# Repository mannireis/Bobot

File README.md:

# Bobot

Ever wondered how a 555 timer IC worked? Here you have it! A 555 IC, made entirely with THT transistors.

## Schematic
 
## PCB

## Features
- Low power design! 3V operating voltage
- Awesome Robot cat design!
- Keychain!

## How to build
Just order the PCB & components, open up the KiCAD file and build it accordingly.

## BOM
- 1 	Battery holder
- 2 	220 ohm resistors
- 1 	Push Button

Made by `@manni` on slack :3

Not copying `@cyao`'s readme trust!

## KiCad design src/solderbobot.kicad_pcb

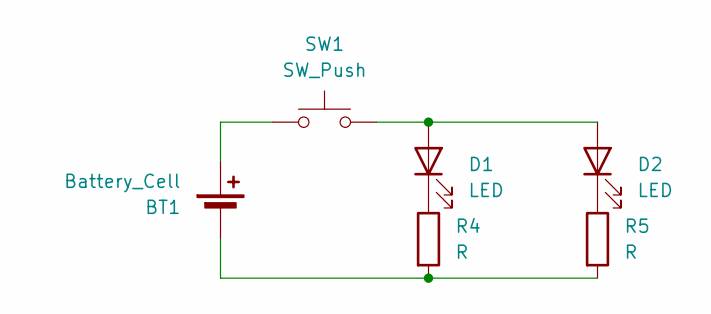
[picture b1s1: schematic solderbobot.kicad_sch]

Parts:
BT1: Battery_Cell; BatteryHolder_Keystone_3034_1x20mm
D1, D2: LED; LED_D5.0mm
R4, R5: R; R_Axial_DIN0207_L6.3mm_D2.5mm_P7.62mm_Horizontal
SW1: SW_Push; SW_PUSH_6mm

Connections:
unnamed: BT1.1 (+), SW1.1
unnamed: BT1.2 (-), R4.2, R5.2
unnamed: D1.2 (A), D2.2 (A), SW1.2
unnamed: D1.1 (K), R4.1
unnamed: D2.1 (K), R5.1

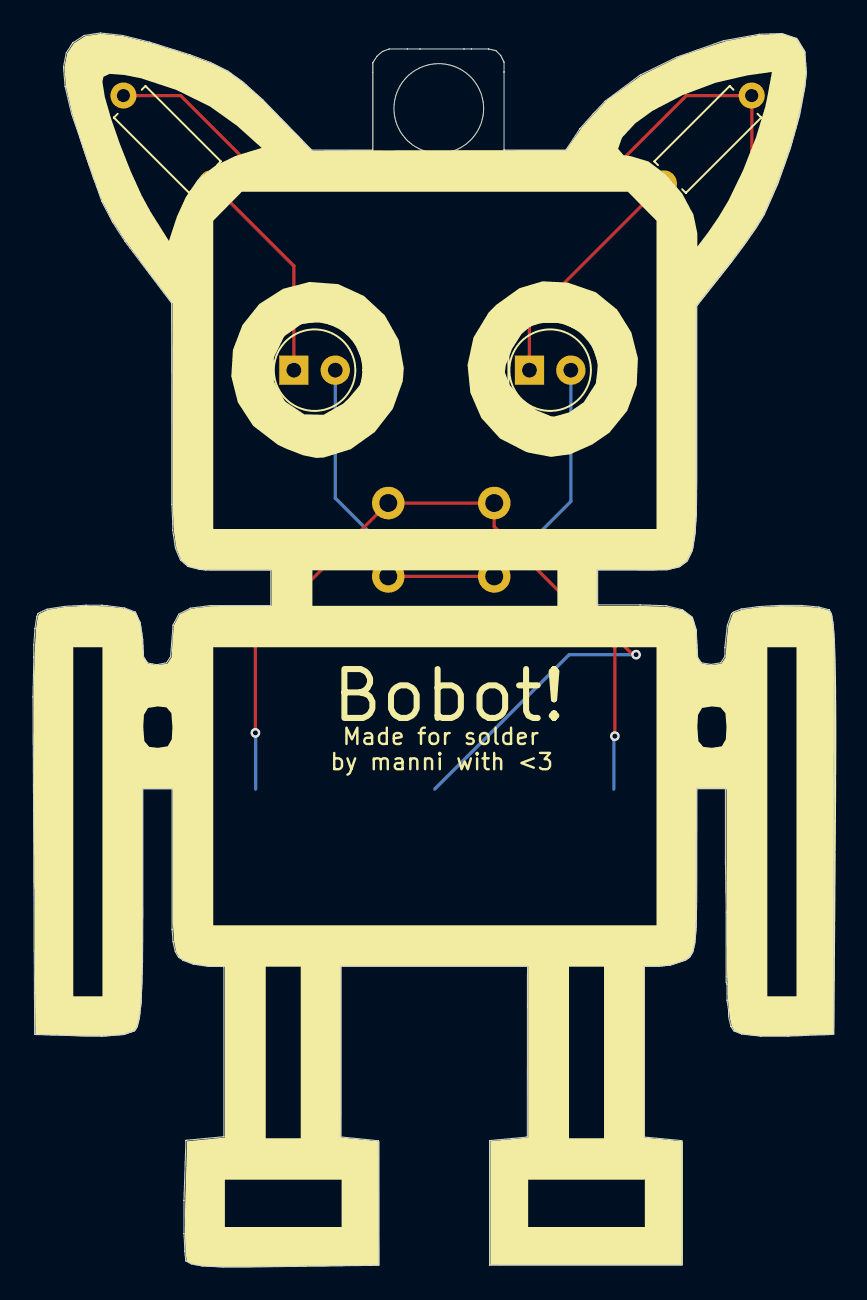
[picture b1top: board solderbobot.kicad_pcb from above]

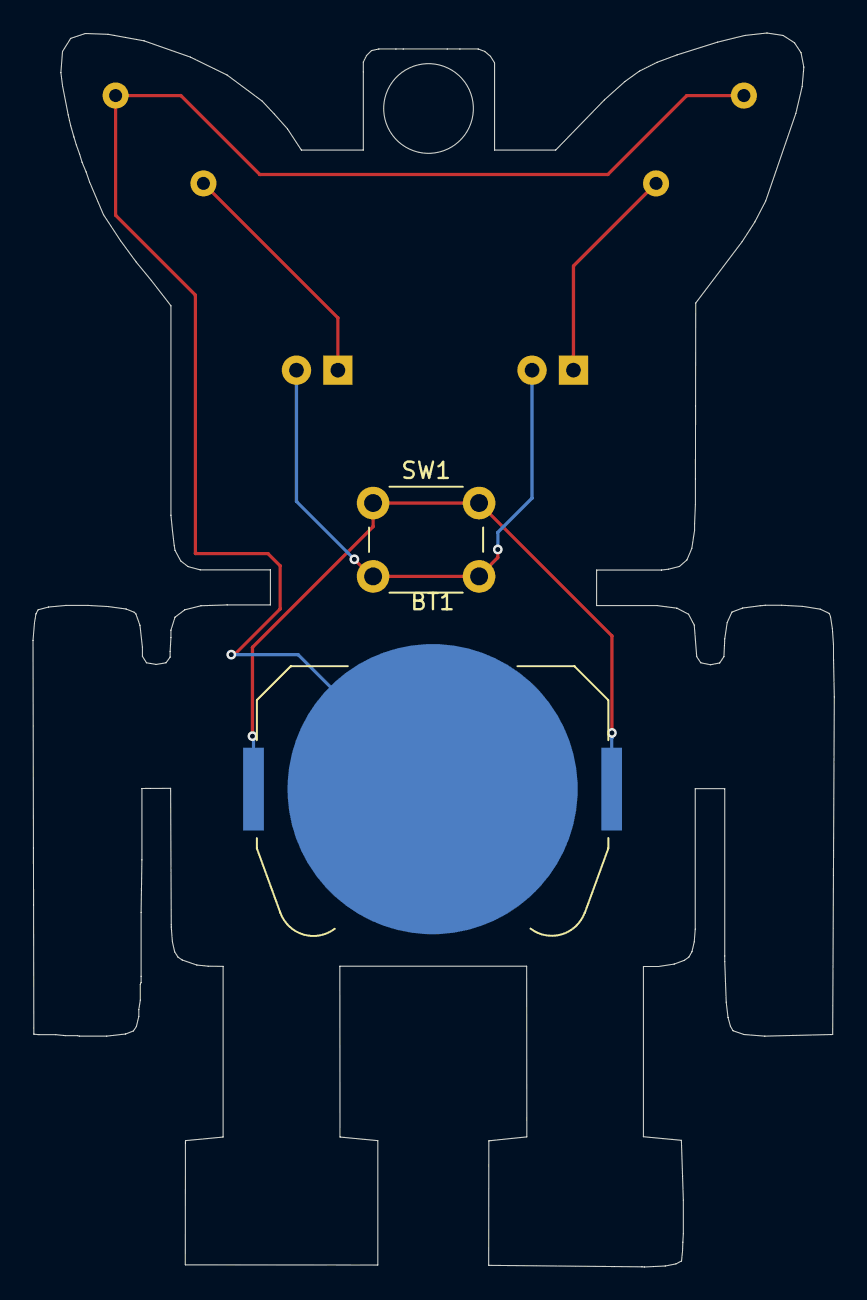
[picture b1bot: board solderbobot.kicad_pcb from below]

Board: 2 copper layers, 49.2 x 75.7 mm, 6 parts (2 on the bottom side), 5 nets.

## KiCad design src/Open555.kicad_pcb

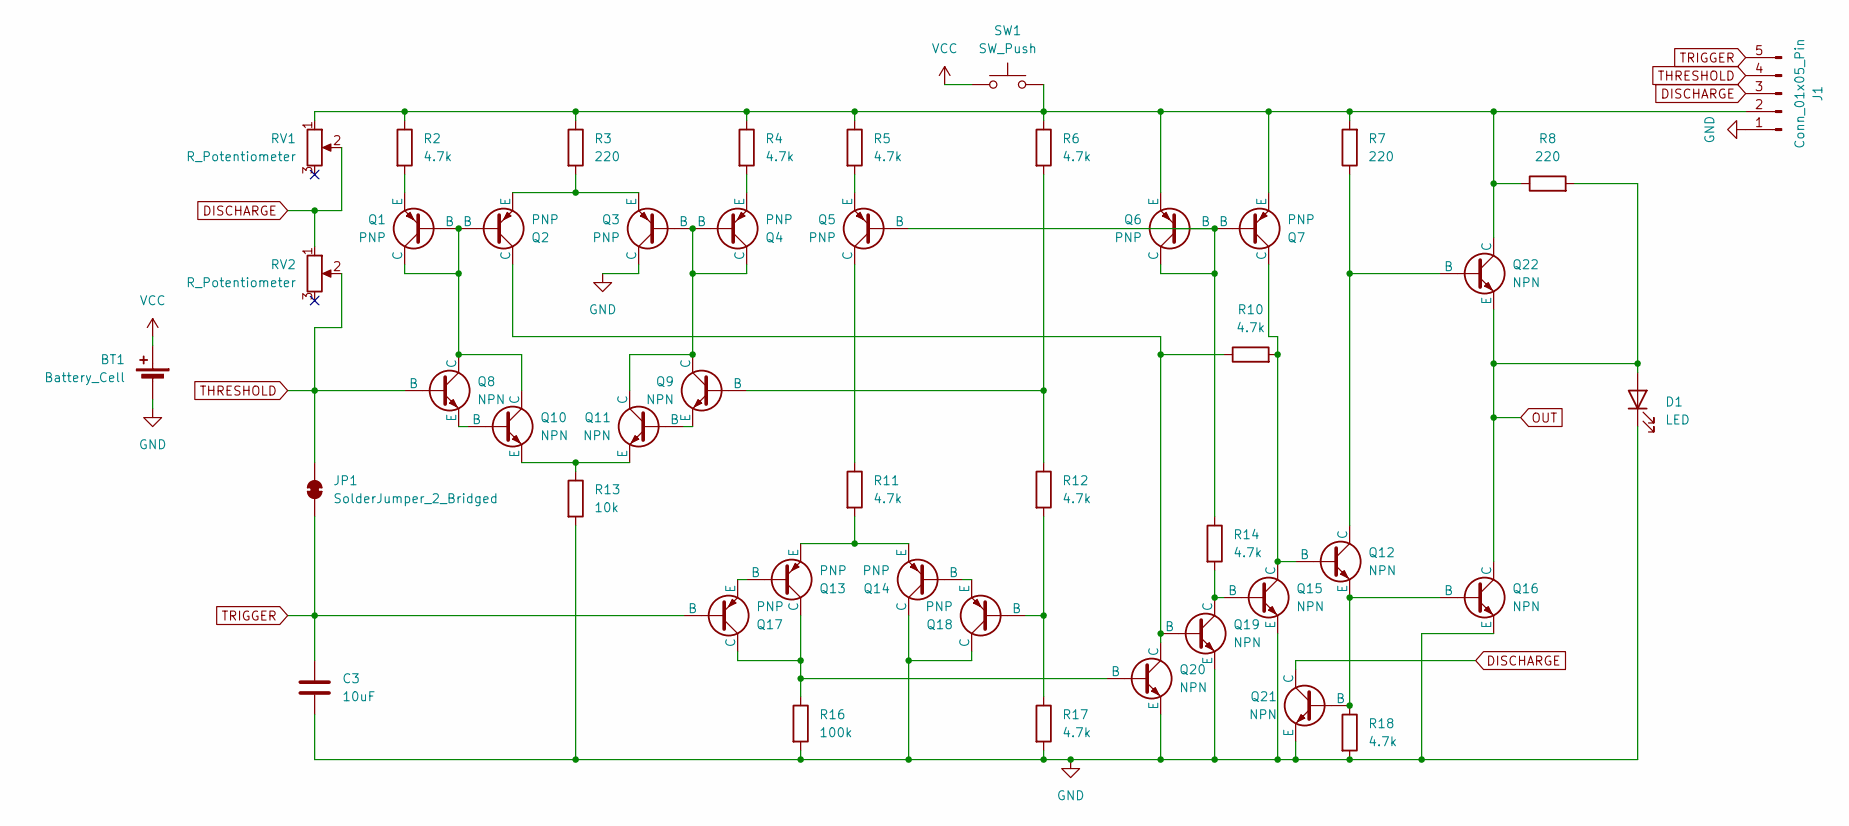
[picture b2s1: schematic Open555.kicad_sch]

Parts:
BT1: Battery_Cell; BatteryHolder_Multicomp_BC-2001_1x2032
C3: 10uF; CP_Radial_D8.0mm_P5.00mm
D1: LED; LED_D5.0mm
J1: Conn_01x05_Pin; PinHeader_1x05_P2.54mm_Vertical
JP1: SolderJumper_2_Bridged; SolderJumper-2_P1.3mm_Bridged2Bar_RoundedPad1.0x1.5mm
Q1, Q2, Q3, Q4, Q5, Q6, Q7, Q13, Q14, Q17, Q18: PNP; TO-92L_HandSolder
Q8, Q9, Q10, Q11, Q12, Q15, Q16, Q19, Q20, Q21, Q22: NPN; TO-92L_HandSolder
R2, R4, R5, R6, R10, R11, R12, R14, R17, R18: 4.7k; R_Axial_DIN0207_L6.3mm_D2.5mm_P7.62mm_Horizontal
R3, R7, R8: 220; R_Axial_DIN0207_L6.3mm_D2.5mm_P7.62mm_Horizontal
R13: 10k; R_Axial_DIN0207_L6.3mm_D2.5mm_P7.62mm_Horizontal
R16: 100k; R_Axial_DIN0207_L6.3mm_D2.5mm_P7.62mm_Horizontal
RV1, RV2: R_Potentiometer; Potentiometer_Runtron_RM-065_Vertical
SW1: SW_Push; SW_PUSH_6mm

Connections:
DISCHARGE: J1.3, Q21.1 (C), RV1.2, RV2.1
GND: BT1.2 (-), C3.2, D1.1 (K), J1.1, Q3.1 (C), Q14.1 (C), Q15.3 (E), Q16.3 (E), Q18.1 (C), Q19.3 (E), Q20.3 (E), Q21.3 (E), R13.2, R16.2, R17.2, R18.2
unnamed: J1.2, Q6.3 (E), Q7.3 (E), Q22.1 (C), R2.1, R3.1, R4.1, R5.1, R6.1, R7.2, R8.1, RV1.1, SW1.2
unnamed: Q1.1 (C), Q1.2 (B), Q2.2 (B), Q8.1 (C), Q10.1 (C)
unnamed: Q1.3 (E), R2.2
unnamed: Q2.3 (E), Q3.3 (E), R3.2
unnamed: Q4.3 (E), R4.2
unnamed: Q5.2 (B), Q6.1 (C), Q6.2 (B), Q7.2 (B), R14.1
unnamed: Q5.1 (C), R11.1
unnamed: Q5.3 (E), R5.2
unnamed: Q9.2 (B), R6.2, R12.1
unnamed: Q8.3 (E), Q10.2 (B)
unnamed: Q10.3 (E), Q11.3 (E), R13.1
unnamed: Q9.3 (E), Q11.2 (B)
unnamed: Q3.2 (B), Q4.1 (C), Q4.2 (B), Q9.1 (C), Q11.1 (C)
unnamed: Q7.1 (C), Q12.2 (B), Q15.1 (C), R10.2
unnamed: Q12.1 (C), Q22.2 (B), R7.1
unnamed: Q12.3 (E), Q16.2 (B), Q21.2 (B), R18.1
unnamed: Q13.2 (B), Q17.3 (E)
unnamed: Q13.1 (C), Q17.1 (C), Q20.2 (B), R16.1
unnamed: Q13.3 (E), Q14.3 (E), R11.2
unnamed: Q14.2 (B), Q18.3 (E)
unnamed: Q15.2 (B), Q19.1 (C), R14.2
unnamed: Q18.2 (B), R12.2, R17.1
unnamed: Q2.1 (C), Q19.2 (B), Q20.1 (C), R10.1
OUT: D1.2 (A), Q16.1 (C), Q22.3 (E), R8.2
THRESHOLD: J1.4, JP1.2 (B), Q8.2 (B), RV2.2
TRIGGER: C3.1, J1.5, JP1.1 (A), Q17.2 (B)
VCC: BT1.1 (+), SW1.1

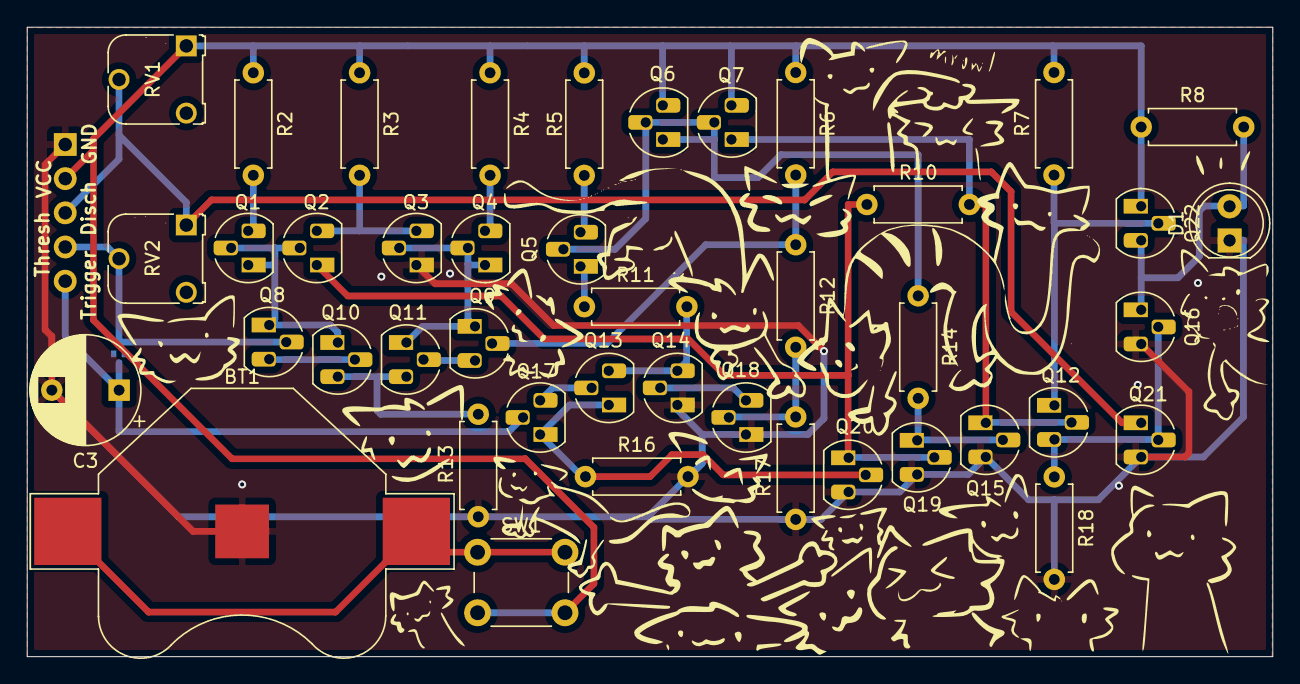
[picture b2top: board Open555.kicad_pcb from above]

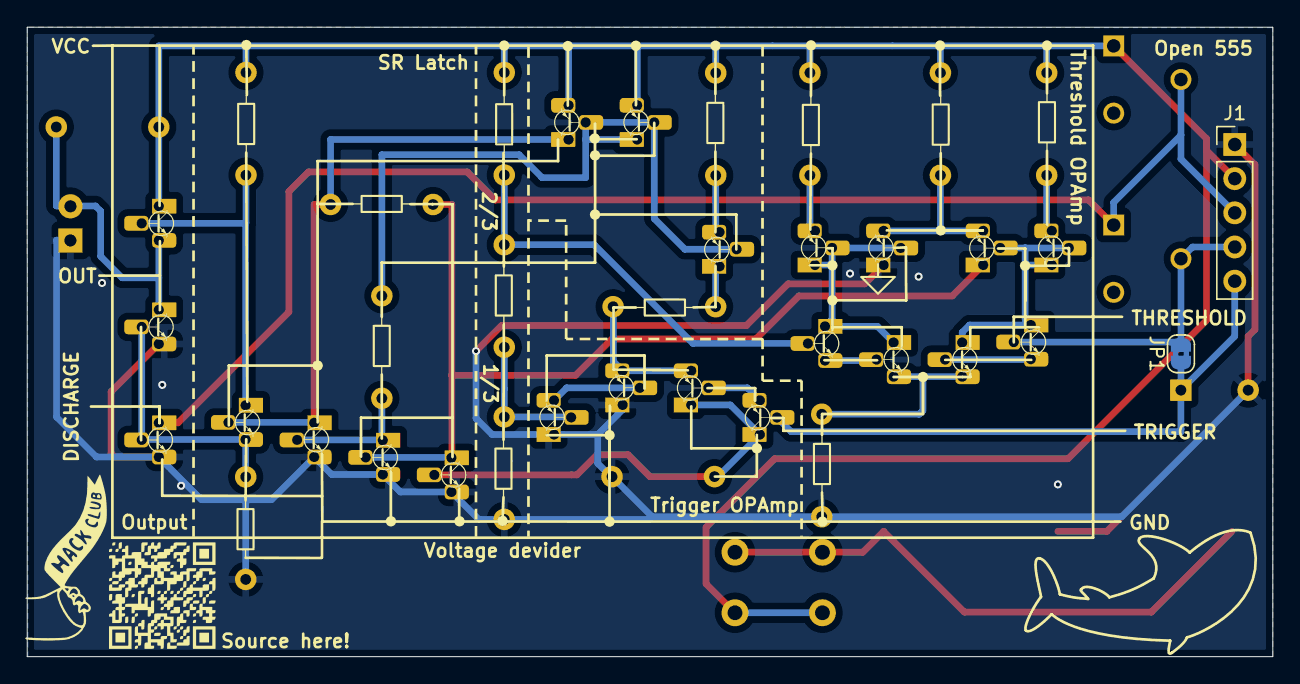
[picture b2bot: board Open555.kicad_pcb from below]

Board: 2 copper layers, 92.6 x 46.8 mm, 45 parts (2 on the bottom side), 29 nets.

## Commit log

2025-03-20 Init
2025-03-23 Add 555 transistor circuit
2025-03-23 Placed transistors
2025-03-24 Sync
2025-03-26 Add 3D models
2025-03-27 Final revision
2025-03-28 Newest version
2025-04-01 More README
2025-04-09 Fix typo
2025-05-15 add src
2025-05-15 Update LICENSE
